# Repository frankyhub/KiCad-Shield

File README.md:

<div align="center">

|[:skull:ISSUE](https://github.com/frankyhub/KiCad-Shield/issues?q=is%3Aissue)|[:speech_balloon: Forum /Discussion](https://github.com/frankyhub/KiCad-Shield/discussions)|[:grey_question:WiKi](https://github.com/frankyhub/KiCad-Shield/wiki)||
|--|--|--|--|
| | | | |
||<a href="https://github.com/frankyhub/KiCad-Shield/issues">|<a href="https://github.com/frankyhub/KiCad-Shield/discussions">|<a href="https://github.com/frankyhub/KiCad-Shield/releases">|
|| <a href="https://github.com/frankyhub/KiCad-Shield/pulse" alt="Activity">| <a href="https://github.com/frankyhub/KiCad-Shield/graphs/traffic">  |<a href="https://github.com/frankyhub?tab=stars"> |
</div>

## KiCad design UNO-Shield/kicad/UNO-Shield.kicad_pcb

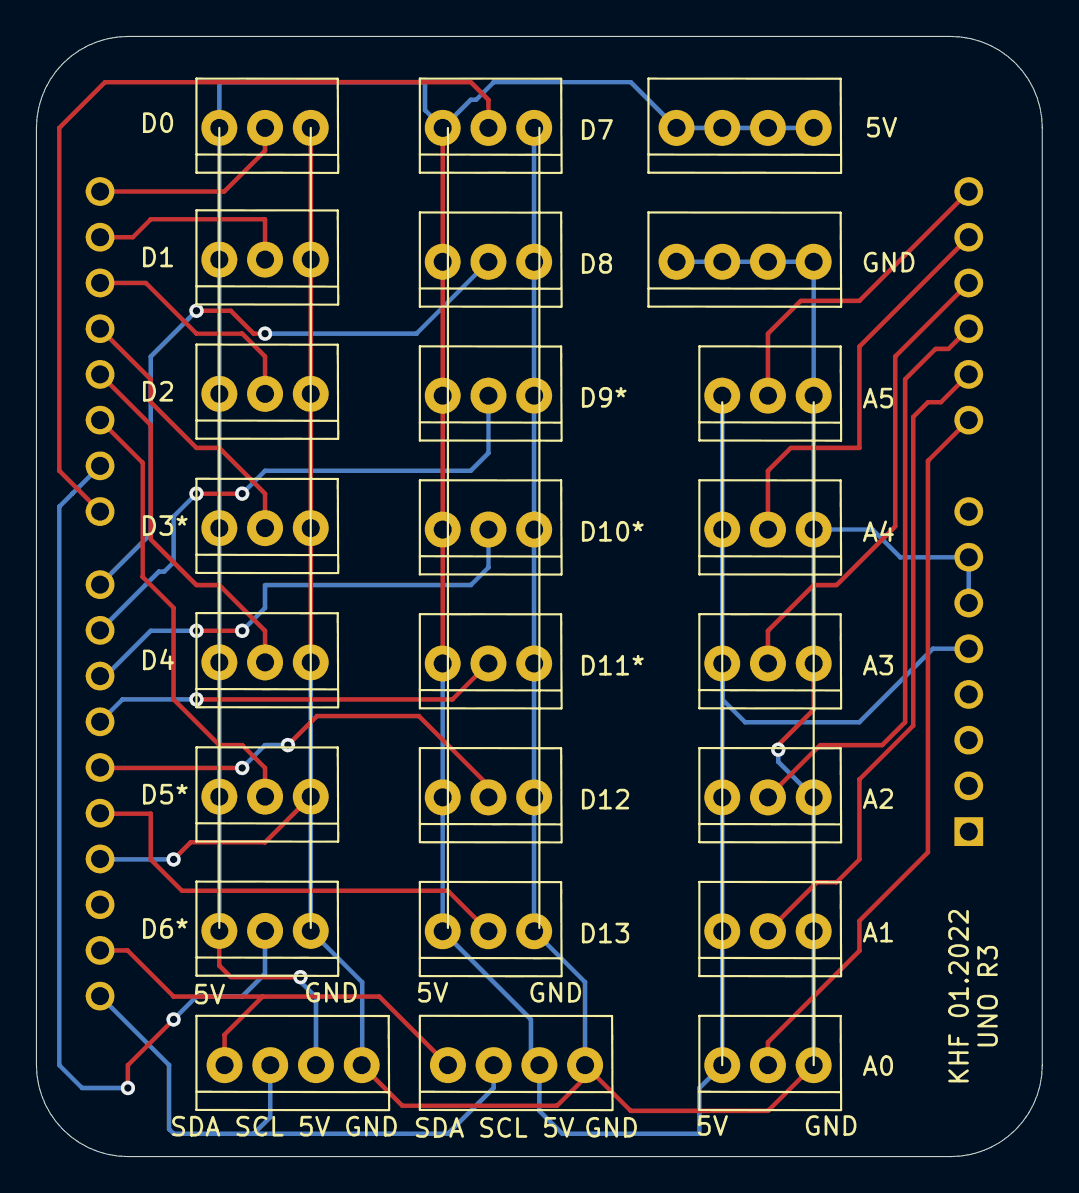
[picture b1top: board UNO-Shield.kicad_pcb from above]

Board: 2 copper layers, 55.9 x 62.2 mm, 25 parts (1 on the bottom side), 24 nets.

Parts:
5V: PL-Stecker_4pol_Data; PL-Stecker4pol
A0, A1, A2, A3, A4, A5: PL-Stecker_3pol; PL-Stecker3pol
A1#2: Arduino_UNO_R3
D0, D1, D2, D3*, D4, D5*, D6*, D7, D8, D9*, D10*, D11*, D12, D13: PL-Stecker_3pol; PL-Stecker3pol
GND: PL-Stecker_4pol_Data; PL-Stecker4pol
SDA SCL: PL-Stecker_4pol_Data; PL-Stecker4pol
SDA SCL 5V GND: PL-Stecker_4pol_Data; PL-Stecker4pol

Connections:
unnamed: 5V.1, 5V.2, 5V.3, 5V.4, A0.3, A1.3, A1#2.5, A2.3, A3.3, A4.3, A5.3, D0.3, D1.3, D2.3, D3*.3, D4.3, D5*.3, D6*.3, D7.3, D8.3, D9*.3, D10*.3, D11*.3, D12.3, D13.3, SDA SCL.2, SDA SCL 5V GND.2
unnamed: A0.2, A1#2.9
unnamed: A1.2, A1#2.10
unnamed: A1#2.11, A2.2
unnamed: A1#2.12, A3.2
unnamed: A1#2.13, A4.2
unnamed: A1#2.14, A5.2
unnamed: A1#2.15, D0.2
unnamed: A1#2.16, D1.2
unnamed: A1#2.17, D2.2
unnamed: A1#2.18, D3*.2
unnamed: A1#2.19, D4.2
unnamed: A1#2.20, D5*.2
unnamed: A1#2.21, D6*.2
unnamed: A1#2.22, D7.2
unnamed: A1#2.23, D8.2
unnamed: A1#2.24, D9*.2
unnamed: A1#2.25, D10*.2
unnamed: A1#2.26, D11*.2
unnamed: A1#2.27, D12.2
unnamed: A1#2.28, D13.2
unnamed: A0.1, A1.1, A1#2.6, A1#2.7, A1#2.29, A2.1, A3.1, A4.1, A5.1, D0.1, D1.1, D2.1, D3*.1, D4.1, D5*.1, D6*.1, D7.1, D8.1, D9*.1, D10*.1, D11*.1, D12.1, D13.1, GND.1, GND.2, GND.3, GND.4, SDA SCL.1, SDA SCL 5V GND.1
unnamed: A1#2.31, SDA SCL.4, SDA SCL 5V GND.4
unnamed: A1#2.32, SDA SCL.3, SDA SCL 5V GND.3

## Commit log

2024-02-23 23-02-2024
2024-02-23 23-02-2023
2024-10-12 V12102024
